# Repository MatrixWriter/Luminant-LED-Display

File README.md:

Luminant LED Display
====================

A large format, ultra bright LED display using printed circuit board technology that uses the Teensy 3.1 microcontroller and OctoWS2811 libraries.  The technology and design behind this project will result in a product that can be used for a broad range of commercial and hobbyist applications. 

LED Type: WS2812B

Designed and engineered by JP Allport <br>

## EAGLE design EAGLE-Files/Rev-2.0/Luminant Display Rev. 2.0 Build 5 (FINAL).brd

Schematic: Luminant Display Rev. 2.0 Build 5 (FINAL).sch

Parts (part):
C1, C2, C3, C4, C5, C6, C7, C8, C9, C10, C11, C12, C13, C14, C15, C16, C17, C18, C19, C20, C21, C22, C23, C24, C25, C26, C27, C28, C29, C30, C31, C32, C33, C34, C35, C36, C37, C38, C39, C40, C41, C42, C43, C44, C45, C46, C47, C48, C49, C50, C51, C52, C53, C54, C55, C56, C57, C58, C59, C60, C101, C102, C103, C104, C105, C106, C107, C108, C109, C110, C111, C112, C113, C114, C115, C116, C117, C118, C119, C120, C121, C122, C123, C124, C125, C126, C127, C128, C129, C130, C131, C132, C133, C134, C135, C136, C137, C138, C139, C140, C141, C142, C143, C144, C145, C146, C147, C148, C149, C150, C151, C152, C153, C154, C155, C156, C157, C158, C159, C160, C161, C162, C163, C164, C165, C166, C167, C168, C169, C170, C171, C172, C173, C174, C175, C176, C177, C178, C179, C180, C181, C182, C183, C184, C185, C186, C187, C188, C189, C190, C191, C192, C193, C194, C195, C196, C197, C198, C199, C200, C201, C202, C203, C204, C205, C206, C207, C208, C209, C210, C211, C212, C213, C214, C215, C216, C217, C218, C219, C220, C261, C262, C263, C264, C265, C266, C267, C268, C269, C270, C271, C272, C273, C274, C275, C276, C277, C278, C279, C280, C281, C282, C283, C284, C285, C286, C287, C288, C289, C290, C291, C292, C293, C294, C295, C296, C297, C298, C299, C300, C301, C302, C303, C304, C305, C306, C307, C308, C309, C310, C311, C312, C313, C314, C315, C316, C317, C318, C319, C320, C321, C322, C323, C324, C325, C326, C327, C328, C329, C330, C331, C332, C333, C334, C335, C336, C337, C338, C339, C340, C341, C342, C343, C344, C345, C346, C347, C348, C349, C350, C351, C352, C353, C354, C355, C356, C357, C358, C359, C360, C361, C362, C363, C364, C365, C366, C367, C368, C369, C370, C371, C372, C373, C374, C375, C376, C377, C378, C379, C380, C421, C422, C423, C424, C425, C426, C427, C428, C429, C430, C431, C432, C433, C434, C435, C436, C437, C438, C439, C440, C441, C442, C443, C444, C445, C446, C447, C448, C449, C450, C451, C452, C453, C454, C455, C456, C457, C458, C459, C460, C461, C462, C463, C464, C465, C466, C467, C468, C469, C470, C471, C472, C473, C474, C475, C476, C477, C478, C479, C480, C481, C482, C483, C484, C485, C486, C487, C488, C489, C490, C491, C492, C493, C494, C495, C496, C497, C498, C499, C500, C501, C502, C503, C504, C505, C506, C507, C508, C509, C510, C511, C512, C513, C514, C515, C516, C517, C518, C519, C520, C521, C522, C523, C524, C525, C526, C527, C528, C529, C530, C531, C532, C533, C534, C535, C536, C537, C538, C539, C540, C581, C582, C583, C584, C585, C586, C587, C588, C589, C590, C591, C592, C593, C594, C595, C596, C597, C598, C599, C600, C601, C602, C603, C604, C605, C606, C607, C608, C609, C610, C611, C612, C613, C614, C615, C616, C617, C618, C619, C620, C621, C622, C623, C624, C625, C626, C627, C628, C629, C630, C631, C632, C633, C634, C635, C636, C637, C638, C639, C640, C641, C642, C643, C644, C645, C646, C647, C648, C649, C650, C651, C652, C653, C654, C655, C656, C657, C658, C659, C660, C661, C662, C663, C664, C665, C666, C667, C668, C669, C670, C671, C672, C673, C674, C675, C676, C677, C678, C679, C680, C681, C682, C683, C684, C685, C686, C687, C688, C689, C690, C691, C692, C693, C694, C695, C696, C697, C698, C699, C700, C741, C742, C743, C744, C745, C746, C747, C748, C749, C750, C751, C752, C753, C754, C755, C756, C757, C758, C759, C760, C761, C762, C763, C764, C765, C766, C767, C768, C769, C770, C771, C772, C773, C774, C775, C776, C777, C778, C779, C780, C781, C782, C783, C784, C785, C786, C787, C788, C789, C790, C791, C792, C793, C794, C795, C796, C797, C798, C799, C800, C801, C802, C803, C804, C805, C806, C807, C808, C809, C810, C811, C812, C813, C814, C815, C816, C817, C818, C819, C820, C821, C822, C823, C824, C825, C826, C827, C828, C829, C830, C831, C832, C833, C834, C835, C836, C837, C838, C839, C840, C841, C842, C843, C844, C845, C846, C847, C848, C849, C850, C851, C852, C853, C854, C855, C856, C857, C858, C859, C860, C901, C902, C903, C904, C905, C906, C907, C908, C909, C910, C911, C912, C913, C914, C915, C916, C917, C918, C919, C920, C921, C922, C923, C924, C925, C926, C927, C928, C929, C930, C931, C932, C933, C934, C935, C936, C937, C938, C939, C940, C941, C942, C943, C944, C945, C946, C947, C948, C949, C950, C951, C952, C953, C954, C955, C956, C957, C958, C959, C960, C961, C962, C963, C964, C965, C966, C967, C968, C969, C970, C971, C972, C973, C974, C975, C976, C977, C978, C979, C980, C981, C982, C983, C984, C985, C986, C987, C988, C989, C990, C991, C992, C993, C994, C995, C996, C997, C998, C999, C1000, C1001, C1002, C1003, C1004, C1005, C1006, C1007, C1008, C1009, C1010, C1011, C1012, C1013, C1014, C1015, C1016, C1017, C1018, C1019, C1020, C1061, C1062, C1063, C1064, C1065, C1066, C1067, C1068, C1069, C1070, C1071, C1072, C1073, C1074, C1075, C1076, C1077, C1078, C1079, C1080, C1081, C1082, C1083, C1084, C1085, C1086, C1087, C1088, C1089, C1090, C1091, C1092, C1093, C1094, C1095, C1096, C1097, C1098, C1099, C1100, C1101, C1102, C1103, C1104, C1105, C1106, C1107, C1108, C1109, C1110, C1111, C1112, C1113, C1114, C1115, C1116, C1117, C1118, C1119, C1120, C1121, C1122, C1123, C1124, C1125, C1126, C1127, C1128, C1129, C1130, C1131, C1132, C1133, C1134, C1135, C1136, C1137, C1138, C1139, C1140, C1141, C1142, C1143, C1144, C1145, C1146, C1147, C1148, C1149, C1150, C1151, C1152, C1153, C1154, C1155, C1156, C1157, C1158, C1159, C1160, C1161, C1162, C1163, C1164, C1165, C1166, C1167, C1168, C1169, C1170, C1171, C1172, C1173, C1174, C1175, C1176, C1177, C1178, C1179, C1180, C1221, C1222, C1223, C1224, C1225, C1226, C1227, C1228, C1229, C1230, C1231, C1232, C1233, C1234, C1235, C1236, C1237, C1238, C1239, C1240, C1241, C1242, C1243, C1244, C1245, C1246, C1247, C1248, C1249, C1250, C1251, C1252, C1253, C1254, C1255, C1256, C1257, C1258, C1259, C1260, C1261, C1262, C1263, C1264, C1265, C1266, C1267, C1268, C1269, C1270, C1271, C1272, C1273, C1274, C1275, C1276, C1277, C1278, C1279, C1280, C1281, C1282, C1283, C1284, C1285, C1286, C1287, C1288, C1289, C1290, C1291, C1292, C1293, C1294, C1295, C1296, C1297, C1298, C1299, C1300, C1301, C1302, C1303, C1304, C1305, C1306, C1307, C1308, C1309, C1310, C1311, C1312, C1313, C1314, C1315, C1316, C1317, C1318, C1319, C1320, C1321, C1322, C1323, C1324, C1325, C1326, C1327, C1328, C1329, C1330, C1331, C1332, C1333, C1334, C1335, C1336, C1337, C1338, C1339, C1340, C1381, C1382, C1383, C1384, C1385, C1386, C1387, C1388, C1389, C1390, C1391, C1392, C1393, C1394, C1395, C1396, C1397, C1398, C1399, C1400, C1401, C1402, C1403, C1404, C1405, C1406, C1407, C1408, C1409, C1410, C1411, C1412, C1413, C1414, C1415, C1416, C1417, C1418, C1419, C1420, C1421, C1422, C1423, C1424, C1425, C1426, C1427, C1428, C1429, C1430, C1431, C1432, C1433, C1434, C1435, C1436, C1437, C1438, C1439, C1440, C1441, C1442, C1443, C1444, C1445, C1446, C1447, C1448, C1449, C1450, C1451, C1452, C1453, C1454, C1455, C1456, C1457, C1458, C1459, C1460, C1461, C1462, C1463, C1464, C1465, C1466, C1467, C1468, C1469, C1470, C1471, C1472, C1473, C1474, C1475, C1476, C1477, C1478, C1479, C1480, C1481, C1482, C1483, C1484, C1485, C1486, C1487, C1488, C1489, C1490, C1491, C1492, C1493, C1494, C1495, C1496, C1497, C1498, C1499, C1500, C1541, C1542, C1543, C1544, C1545, C1546, C1547, C1548, C1549, C1550, C1551, C1552, C1553, C1554, C1555, C1556, C1557, C1558, C1559, C1560, C1561, C1562, C1563, C1564, C1565, C1566, C1567, C1568, C1569, C1570, C1571, C1572, C1573, C1574, C1575, C1576, C1577, C1578, C1579, C1580, C1581, C1582, C1583, C1584, C1585, C1586, C1587, C1588, C1589, C1590, C1591, C1592, C1593, C1594, C1595, C1596, C1597, C1598, C1599, C1600, C1601, C1602, C1603, C1604, C1605, C1606, C1607, C1608, C1609, C1610, C1611, C1612, C1613, C1614, C1615, C1616, C1617, C1618, C1619, C1620, C1621, C1622, C1623, C1624, C1625, C1626, C1627, C1628, C1629, C1630, C1631, C1632, C1633, C1634, C1635, C1636, C1637, C1638, C1639, C1640, C1641, C1642, C1643, C1644, C1645, C1646, C1647, C1648, C1649, C1650, C1651, C1652, C1653, C1654, C1655, C1656, C1657, C1658, C1659, C1660, C1701, C1702, C1703, C1704, C1705, C1706, C1707, C1708, C1709, C1710, C1711, C1712, C1713, C1714, C1715, C1716, C1717, C1718, C1719, C1720, C1721, C1722, C1723, C1724, C1725, C1726, C1727, C1728, C1729, C1730, C1731, C1732, C1733, C1734, C1735, C1736, C1737, C1738, C1739, C1740, C1741, C1742, C1743, C1744, C1745, C1746, C1747, C1748, C1749, C1750, C1751, C1752, C1753, C1754, C1755, C1756, C1757, C1758, C1759, C1760, C1761, C1762, C1763, C1764, C1765, C1766, C1767, C1768, C1769, C1770, C1771, C1772, C1773, C1774, C1775, C1776, C1777, C1778, C1779, C1780, C1781, C1782, C1783, C1784, C1785, C1786, C1787, C1788, C1789, C1790, C1791, C1792, C1793, C1794, C1795, C1796, C1797, C1798, C1799, C1800, C1801, C1802, C1803, C1804, C1805, C1806, C1807, C1808, C1809, C1810, C1811, C1812, C1813, C1814, C1815, C1816, C1817, C1818, C1819, C1820, C1861, C1862, C1863, C1864, C1865, C1866, C1867, C1868, C1869, C1870, C1871, C1872, C1873, C1874, C1875, C1876, C1877, C1878, C1879, C1880, C1881, C1882, C1883, C1884, C1885, C1886, C1887, C1888, C1889, C1890, C1891, C1892, C1893, C1894, C1895, C1896, C1897, C1898, C1899, C1900, C1901, C1902, C1903, C1904, C1905, C1906, C1907, C1908, C1909, C1910, C1911, C1912, C1913, C1914, C1915, C1916, C1917, C1918, C1919, C1920, C1921, C1922, C1923, C1924, C1925, C1926, C1927, C1928, C1929, C1930, C1931, C1932, C1933, C1934, C1935, C1936, C1937, C1938, C1939, C1940, C1941, C1942, C1943, C1944, C1945, C1946, C1947, C1948, C1949, C1950, C1951, C1952, C1953, C1954, C1955, C1956, C1957, C1958, C1959, C1960, C1961, C1962, C1963, C1964, C1965, C1966, C1967, C1968, C1969, C1970, C1971, C1972, C1973, C1974, C1975, C1976, C1977, C1978, C1979, C1980, C2021, C2022, C2023, C2024, C2025, C2026, C2027, C2028, C2029, C2030, C2031, C2032, C2033, C2034, C2035, C2036, C2037, C2038, C2039, C2040, C2041, C2042, C2043, C2044, C2045, C2046, C2047, C2048, C2049, C2050, C2051, C2052, C2053, C2054, C2055, C2056, C2057, C2058, C2059, C2060, C2061, C2062, C2063, C2064, C2065, C2066, C2067, C2068, C2069, C2070, C2071, C2072, C2073, C2074, C2075, C2076, C2077, C2078, C2079, C2080, C2081, C2082, C2083, C2084, C2085, C2086, C2087, C2088, C2089, C2090, C2091, C2092, C2093, C2094, C2095, C2096, C2097, C2098, C2099, C2100, C2101, C2102, C2103, C2104, C2105, C2106, C2107, C2108, C2109, C2110, C2111, C2112, C2113, C2114, C2115, C2116, C2117, C2118, C2119, C2120, C2121, C2122, C2123, C2124, C2125, C2126, C2127, C2128, C2129, C2130, C2131, C2132, C2133, C2134, C2135, C2136, C2137, C2138, C2139, C2140, C2181, C2182, C2183, C2184, C2185, C2186, C2187, C2188, C2189, C2190, C2191, C2192, C2193, C2194, C2195, C2196, C2197, C2198, C2199, C2200, C2201, C2202, C2203, C2204, C2205, C2206, C2207, C2208, C2209, C2210, C2211, C2212, C2213, C2214, C2215, C2216, C2217, C2218, C2219, C2220, C2221, C2222, C2223, C2224, C2225, C2226, C2227, C2228, C2229, C2230, C2231, C2232, C2233, C2234, C2235, C2236, C2237, C2238, C2239, C2240, C2241, C2242, C2243, C2244, C2245, C2246, C2247, C2248, C2249, C2250, C2251, C2252, C2253, C2254, C2255, C2256, C2257, C2258, C2259, C2260, C2261, C2262, C2263, C2264, C2265, C2266, C2267, C2268, C2269, C2270, C2271, C2272, C2273, C2274, C2275, C2276, C2277, C2278, C2279, C2280, C2281, C2282, C2283, C2284, C2285, C2286, C2287, C2288, C2289, C2290, C2291, C2292, C2293, C2294, C2295, C2296, C2297, C2298, C2299, C2300, C2341, C2342, C2343, C2344, C2345, C2346, C2347, C2348, C2349, C2350, C2351, C2352, C2353, C2354, C2355, C2356, C2357, C2358, C2359, C2360, C2361, C2362, C2363, C2364, C2365, C2366, C2367, C2368, C2369, C2370, C2371, C2372, C2373, C2374, C2375, C2376, C2377, C2378, C2379, C2380, C2381, C2382, C2383, C2384, C2385, C2386, C2387, C2388, C2389, C2390, C2391, C2392, C2393, C2394, C2395, C2396, C2397, C2398, C2399, C2400, C2401, C2402, C2403, C2404, C2405, C2406, C2407, C2408, C2409, C2410, C2411, C2412, C2413, C2414, C2415, C2416, C2417, C2418, C2419, C2420, C2421, C2422, C2423, C2424, C2425, C2426, C2427, C2428, C2429, C2430, C2431, C2432, C2433, C2434, C2435, C2436, C2437, C2438, C2439, C2440, C2441, C2442, C2443, C2444, C2445, C2446, C2447, C2448, C2449, C2450, C2451, C2452, C2453, C2454, C2455, C2456, C2457, C2458, C2459, C2460, C2501, C2502, C2503, C2504, C2505, C2506, C2507, C2508, C2509, C2510, C2511, C2512, C2513, C2514, C2515, C2516, C2517, C2518, C2519, C2520, C2521, C2522, C2523, C2524, C2525, C2526, C2527, C2528, C2529, C2530, C2531, C2532, C2533, C2534, C2535, C2536, C2537, C2538, C2539, C2540, C2541, C2542, C2543, C2544, C2545, C2546, C2547, C2548, C2549, C2550, C2551, C2552, C2553, C2554, C2555, C2556, C2557, C2558, C2559, C2560: 0.1uF; 0805
C61, C64: CPOL-EU-PANASONIC_FK_V_H; PANASONIC_FK_V_H
C62, C63: CAP_POLE; PANASONIC_E
C65: CAP_POLC; PANASONIC_C
CAP-IC1-OPTIONAL, CAP-IC2-OPTIONAL: 0.1uF; 1206
IC1, IC2: 74HCT245N; DIL20
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
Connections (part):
3.3V: TEENSY1.3.3V, TEENSY1.3.3V1 (3.3V), TEENSY2.3.3V, TEENSY2.3.3V1 (3.3V)
5V-POWER: C1.1, C2.1, C3.1, C4.1, C5.1, C6.1, C7.1, C8.1, C9.1, C10.1, C11.1, C12.1, C13.1, C14.1, C15.1, C16.1, C17.1, C18.1, C19.1, C20.1, C21.1, C22.1, C23.1, C24.1, C25.1, C26.1, C27.1, C28.1, C29.1, C30.1, C31.1, C32.1, C33.1, C34.1, C35.1, C36.1, C37.1, C38.1, C39.1, C40.1, C41.1, C42.1, C43.1, C44.1, C45.1, C46.1, C47.1, C48.1, C49.1, C50.1, C51.1, C52.1, C53.1, C54.1, C55.1, C56.1, C57.1, C58.1, C59.1, C60.1, C61.+, C62.+, C63.+, C64.+, C101.1, C102.1, C103.1, C104.1, C105.1, C106.1, C107.1, C108.1, C109.1, C110.1, C111.1, C112.1, C113.1, C114.1, C115.1, C116.1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
AGND: TEENSY1.AGND, TEENSY2.AGND
DIN-1-IC1: LED60.4 (DI), R16.2
DIN-1-IC2: LED1340.4 (DI), R32.2
DIN-2-IC1: LED220.4 (DI), R15.2
DIN-2-IC2: LED1500.4 (DI), R31.2
DIN-3-IC1: LED380.4 (DI), R14.2
DIN-3-IC2: LED1660.4 (DI), R30.2
DIN-4-IC1: LED540.4 (DI), R13.2
DIN-4-IC2: LED1820.4 (DI), R29.2
DIN-5-IC1: LED700.4 (DI), R12.2
DIN-5-IC2: LED1980.4 (DI), R28.2
DIN-6-IC1: LED860.4 (DI), R11.2
DIN-6-IC2: LED2140.4 (DI), R27.2
DIN-7-IC1: LED1020.4 (DI), R10.2
DIN-7-IC2: LED2300.4 (DI), R26.2
DIN-8-IC1: LED1180.4 (DI), R9.2
DIN-8-IC2: LED2460.4 (DI), R25.2
FRAME-SYNC: TEENSY1.12 (12/MISO), TEENSY2.12 (12/MISO)
GND: C1.2, C2.2, C3.2, C4.2, C5.2, C6.2, C7.2, C8.2, C9.2, C10.2, C11.2, C12.2, C13.2, C14.2, C15.2, C16.2, C17.2, C18.2, C19.2, C20.2, C21.2, C22.2, C23.2, C24.2, C25.2, C26.2, C27.2, C28.2, C29.2, C30.2, C31.2, C32.2, C33.2, C34.2, C35.2, C36.2, C37.2, C38.2, C39.2, C40.2, C41.2, C42.2, C43.2, C44.2, C45.2, C46.2, C47.2, C48.2, C49.2, C50.2, C51.2, C52.2, C53.2, C54.2, C55.2, C56.2, C57.2, C58.2, C59.2, C60.2, C61.-, C62.-, C63.-, C64.-, C65.-, C101.2, C102.2, C103.2, C104.2, C105.2, C106.2, C107.2, C108.2, C109.2, C110.2, C111.2, C112.2, C113.2, C114.2, C115.2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
unnamed: LED1.4 (DI), LED2.2 (DO)
unnamed: LED3.4 (DI), LED4.2 (DO)
unnamed: LED2.4 (DI), LED3.2 (DO)
unnamed: LED5.4 (DI), LED6.2 (DO)
unnamed: LED7.4 (DI), LED8.2 (DO)
unnamed: LED6.4 (DI), LED7.2 (DO)
unnamed: LED4.4 (DI), LED5.2 (DO)
unnamed: LED9.4 (DI), LED10.2 (DO)
unnamed: LED11.4 (DI), LED12.2 (DO)
unnamed: LED10.4 (DI), LED11.2 (DO)
unnamed: LED13.4 (DI), LED14.2 (DO)
unnamed: LED15.4 (DI), LED16.2 (DO)
unnamed: LED14.4 (DI), LED15.2 (DO)
unnamed: LED12.4 (DI), LED13.2 (DO)
unnamed: LED8.4 (DI), LED9.2 (DO)
unnamed: LED17.4 (DI), LED18.2 (DO)
unnamed: LED19.4 (DI), LED20.2 (DO)
unnamed: LED18.4 (DI), LED19.2 (DO)
unnamed: LED21.4 (DI), LED22.2 (DO)
unnamed: LED23.4 (DI), LED24.2 (DO)
unnamed: LED22.4 (DI), LED23.2 (DO)
unnamed: LED20.4 (DI), LED21.2 (DO)
unnamed: LED25.4 (DI), LED26.2 (DO)
unnamed: LED27.4 (DI), LED28.2 (DO)
unnamed: LED26.4 (DI), LED27.2 (DO)
unnamed: LED29.4 (DI), LED30.2 (DO)
unnamed: LED31.4 (DI), LED32.2 (DO)
unnamed: LED30.4 (DI), LED31.2 (DO)
unnamed: LED28.4 (DI), LED29.2 (DO)
unnamed: LED24.4 (DI), LED25.2 (DO)
unnamed: LED16.4 (DI), LED17.2 (DO)
unnamed: LED33.4 (DI), LED34.2 (DO)
unnamed: LED35.4 (DI), LED36.2 (DO)
unnamed: LED34.4 (DI), LED35.2 (DO)
unnamed: LED37.4 (DI), LED38.2 (DO)
unnamed: LED39.4 (DI), LED40.2 (DO)
unnamed: LED38.4 (DI), LED39.2 (DO)
unnamed: LED36.4 (DI), LED37.2 (DO)
unnamed: LED41.4 (DI), LED42.2 (DO)
unnamed: LED43.4 (DI), LED44.2 (DO)
unnamed: LED42.4 (DI), LED43.2 (DO)
unnamed: LED45.4 (DI), LED46.2 (DO)
unnamed: LED47.4 (DI), LED48.2 (DO)
unnamed: LED46.4 (DI), LED47.2 (DO)
unnamed: LED44.4 (DI), LED45.2 (DO)
unnamed: LED40.4 (DI), LED41.2 (DO)
unnamed: LED49.4 (DI), LED50.2 (DO)
unnamed: LED51.4 (DI), LED52.2 (DO)
unnamed: LED50.4 (DI), LED51.2 (DO)
unnamed: LED53.4 (DI), LED54.2 (DO)
unnamed: LED55.4 (DI), LED56.2 (DO)
unnamed: LED54.4 (DI), LED55.2 (DO)
unnamed: LED52.4 (DI), LED53.2 (DO)
unnamed: LED57.4 (DI), LED58.2 (DO)
unnamed: LED59.4 (DI), LED60.2 (DO)
unnamed: LED58.4 (DI), LED59.2 (DO)
unnamed: LED56.4 (DI), LED57.2 (DO)
unnamed: LED48.4 (DI), LED49.2 (DO)
unnamed: LED32.4 (DI), LED33.2 (DO)
unnamed: IC2.1 (DIR), VCC-PAD11.TP
unnamed: LED101.4 (DI), LED102.2 (DO)
unnamed: LED103.4 (DI), LED104.2 (DO)
unnamed: LED102.4 (DI), LED103.2 (DO)
unnamed: LED105.4 (DI), LED106.2 (DO)
unnamed: LED107.4 (DI), LED108.2 (DO)
unnamed: LED106.4 (DI), LED107.2 (DO)
unnamed: LED109.4 (DI), LED110.2 (DO)
unnamed: LED111.4 (DI), LED112.2 (DO)
unnamed: LED110.4 (DI), LED111.2 (DO)
unnamed: LED108.4 (DI), LED109.2 (DO)
unnamed: LED104.4 (DI), LED105.2 (DO)
unnamed: LED113.4 (DI), LED114.2 (DO)
unnamed: LED115.4 (DI), LED116.2 (DO)
unnamed: LED114.4 (DI), LED115.2 (DO)
unnamed: LED117.4 (DI), LED118.2 (DO)
unnamed: LED119.4 (DI), LED120.2 (DO)
unnamed: LED118.4 (DI), LED119.2 (DO)
unnamed: LED116.4 (DI), LED117.2 (DO)
unnamed: LED121.4 (DI), LED122.2 (DO)
unnamed: LED123.4 (DI), LED124.2 (DO)
unnamed: LED122.4 (DI), LED123.2 (DO)
unnamed: LED125.4 (DI), LED126.2 (DO)
unnamed: LED127.4 (DI), LED128.2 (DO)
unnamed: LED126.4 (DI), LED127.2 (DO)
unnamed: LED124.4 (DI), LED125.2 (DO)
unnamed: LED120.4 (DI), LED121.2 (DO)
unnamed: LED129.4 (DI), LED130.2 (DO)
unnamed: LED131.4 (DI), LED132.2 (DO)
unnamed: LED130.4 (DI), LED131.2 (DO)
unnamed: LED133.4 (DI), LED134.2 (DO)
unnamed: LED135.4 (DI), LED136.2 (DO)
unnamed: LED134.4 (DI), LED135.2 (DO)
unnamed: LED132.4 (DI), LED133.2 (DO)
unnamed: LED137.4 (DI), LED138.2 (DO)
unnamed: LED139.4 (DI), LED140.2 (DO)
unnamed: LED138.4 (DI), LED139.2 (DO)
unnamed: LED141.4 (DI), LED142.2 (DO)
unnamed: LED143.4 (DI), LED144.2 (DO)
unnamed: LED142.4 (DI), LED143.2 (DO)
unnamed: LED140.4 (DI), LED141.2 (DO)
unnamed: LED136.4 (DI), LED137.2 (DO)
unnamed: LED128.4 (DI), LED129.2 (DO)
unnamed: LED112.4 (DI), LED113.2 (DO)
unnamed: LED144.4 (DI), LED145.2 (DO)
unnamed: LED146.4 (DI), LED147.2 (DO)
unnamed: LED148.4 (DI), LED149.2 (DO)
unnamed: LED147.4 (DI), LED148.2 (DO)
unnamed: LED150.4 (DI), LED151.2 (DO)
unnamed: LED152.4 (DI), LED153.2 (DO)
unnamed: LED151.4 (DI), LED152.2 (DO)
unnamed: LED149.4 (DI), LED150.2 (DO)
unnamed: LED154.4 (DI), LED155.2 (DO)
unnamed: LED156.4 (DI), LED157.2 (DO)
unnamed: LED155.4 (DI), LED156.2 (DO)
unnamed: LED158.4 (DI), LED159.2 (DO)
unnamed: LED159.4 (DI), LED160.2 (DO)
unnamed: LED157.4 (DI), LED158.2 (DO)
unnamed: LED153.4 (DI), LED154.2 (DO)
unnamed: LED145.4 (DI), LED146.2 (DO)
unnamed: LED161.4 (DI), LED162.2 (DO)
unnamed: LED163.4 (DI), LED164.2 (DO)
unnamed: LED162.4 (DI), LED163.2 (DO)
unnamed: LED165.4 (DI), LED166.2 (DO)
unnamed: LED167.4 (DI), LED168.2 (DO)
unnamed: LED166.4 (DI), LED167.2 (DO)
unnamed: LED164.4 (DI), LED165.2 (DO)
unnamed: LED169.4 (DI), LED170.2 (DO)
unnamed: LED171.4 (DI), LED172.2 (DO)
unnamed: LED170.4 (DI), LED171.2 (DO)
unnamed: LED173.4 (DI), LED174.2 (DO)
unnamed: LED175.4 (DI), LED176.2 (DO)
unnamed: LED174.4 (DI), LED175.2 (DO)
unnamed: LED172.4 (DI), LED173.2 (DO)
unnamed: LED168.4 (DI), LED169.2 (DO)
unnamed: LED177.4 (DI), LED178.2 (DO)
unnamed: LED179.4 (DI), LED180.2 (DO)
unnamed: LED178.4 (DI), LED179.2 (DO)
unnamed: LED181.4 (DI), LED182.2 (DO)
unnamed: LED183.4 (DI), LED184.2 (DO)
unnamed: LED182.4 (DI), LED183.2 (DO)
unnamed: LED180.4 (DI), LED181.2 (DO)
unnamed: LED185.4 (DI), LED186.2 (DO)
unnamed: LED187.4 (DI), LED188.2 (DO)
unnamed: LED186.4 (DI), LED187.2 (DO)
unnamed: LED189.4 (DI), LED190.2 (DO)
unnamed: LED191.4 (DI), LED192.2 (DO)
unnamed: LED190.4 (DI), LED191.2 (DO)
unnamed: LED188.4 (DI), LED189.2 (DO)
unnamed: LED184.4 (DI), LED185.2 (DO)
unnamed: LED176.4 (DI), LED177.2 (DO)
unnamed: LED193.4 (DI), LED194.2 (DO)
unnamed: LED195.4 (DI), LED196.2 (DO)
unnamed: LED194.4 (DI), LED195.2 (DO)
unnamed: LED197.4 (DI), LED198.2 (DO)
unnamed: LED199.4 (DI), LED200.2 (DO)
unnamed: LED198.4 (DI), LED199.2 (DO)
unnamed: LED196.4 (DI), LED197.2 (DO)
unnamed: LED201.4 (DI), LED202.2 (DO)
unnamed: LED203.4 (DI), LED204.2 (DO)
unnamed: LED202.4 (DI), LED203.2 (DO)
unnamed: LED205.4 (DI), LED206.2 (DO)
unnamed: LED207.4 (DI), LED208.2 (DO)
unnamed: LED206.4 (DI), LED207.2 (DO)
unnamed: LED204.4 (DI), LED205.2 (DO)
unnamed: LED200.4 (DI), LED201.2 (DO)
unnamed: LED209.4 (DI), LED210.2 (DO)
unnamed: LED211.4 (DI), LED212.2 (DO)
unnamed: LED210.4 (DI), LED211.2 (DO)
unnamed: LED213.4 (DI), LED214.2 (DO)
unnamed: LED215.4 (DI), LED216.2 (DO)
unnamed: LED214.4 (DI), LED215.2 (DO)
unnamed: LED212.4 (DI), LED213.2 (DO)
unnamed: LED217.4 (DI), LED218.2 (DO)
unnamed: LED219.4 (DI), LED220.2 (DO)
unnamed: LED218.4 (DI), LED219.2 (DO)
unnamed: LED216.4 (DI), LED217.2 (DO)
unnamed: LED208.4 (DI), LED209.2 (DO)
unnamed: LED192.4 (DI), LED193.2 (DO)
unnamed: LED261.4 (DI), LED262.2 (DO)
unnamed: LED263.4 (DI), LED264.2 (DO)
unnamed: LED262.4 (DI), LED263.2 (DO)
unnamed: LED265.4 (DI), LED266.2 (DO)
unnamed: LED267.4 (DI), LED268.2 (DO)
unnamed: LED266.4 (DI), LED267.2 (DO)
unnamed: LED269.4 (DI), LED270.2 (DO)
unnamed: LED271.4 (DI), LED272.2 (DO)
unnamed: LED270.4 (DI), LED271.2 (DO)
unnamed: LED268.4 (DI), LED269.2 (DO)
unnamed: LED264.4 (DI), LED265.2 (DO)
unnamed: LED273.4 (DI), LED274.2 (DO)
unnamed: LED275.4 (DI), LED276.2 (DO)
unnamed: LED274.4 (DI), LED275.2 (DO)
unnamed: LED277.4 (DI), LED278.2 (DO)
unnamed: LED279.4 (DI), LED280.2 (DO)
unnamed: LED278.4 (DI), LED279.2 (DO)
unnamed: LED276.4 (DI), LED277.2 (DO)
unnamed: LED281.4 (DI), LED282.2 (DO)
unnamed: LED283.4 (DI), LED284.2 (DO)
unnamed: LED282.4 (DI), LED283.2 (DO)
unnamed: LED285.4 (DI), LED286.2 (DO)
unnamed: LED287.4 (DI), LED288.2 (DO)
unnamed: LED286.4 (DI), LED287.2 (DO)
unnamed: LED284.4 (DI), LED285.2 (DO)
unnamed: LED280.4 (DI), LED281.2 (DO)
unnamed: LED289.4 (DI), LED290.2 (DO)
unnamed: LED291.4 (DI), LED292.2 (DO)
unnamed: LED290.4 (DI), LED291.2 (DO)
unnamed: LED293.4 (DI), LED294.2 (DO)
unnamed: LED295.4 (DI), LED296.2 (DO)
unnamed: LED294.4 (DI), LED295.2 (DO)
unnamed: LED292.4 (DI), LED293.2 (DO)
unnamed: LED297.4 (DI), LED298.2 (DO)
unnamed: LED299.4 (DI), LED300.2 (DO)
unnamed: LED298.4 (DI), LED299.2 (DO)
unnamed: LED301.4 (DI), LED302.2 (DO)
unnamed: LED303.4 (DI), LED304.2 (DO)
unnamed: LED302.4 (DI), LED303.2 (DO)
unnamed: LED300.4 (DI), LED301.2 (DO)
unnamed: LED296.4 (DI), LED297.2 (DO)
unnamed: LED288.4 (DI), LED289.2 (DO)
unnamed: LED272.4 (DI), LED273.2 (DO)
unnamed: LED304.4 (DI), LED305.2 (DO)
unnamed: LED306.4 (DI), LED307.2 (DO)
unnamed: LED308.4 (DI), LED309.2 (DO)
unnamed: LED307.4 (DI), LED308.2 (DO)
unnamed: LED310.4 (DI), LED311.2 (DO)
unnamed: LED312.4 (DI), LED313.2 (DO)
unnamed: LED311.4 (DI), LED312.2 (DO)
unnamed: LED309.4 (DI), LED310.2 (DO)
unnamed: LED314.4 (DI), LED315.2 (DO)
unnamed: LED316.4 (DI), LED317.2 (DO)
unnamed: LED315.4 (DI), LED316.2 (DO)
unnamed: LED318.4 (DI), LED319.2 (DO)
unnamed: LED319.4 (DI), LED320.2 (DO)
unnamed: LED317.4 (DI), LED318.2 (DO)
unnamed: LED313.4 (DI), LED314.2 (DO)
unnamed: LED305.4 (DI), LED306.2 (DO)
unnamed: LED321.4 (DI), LED322.2 (DO)
unnamed: LED323.4 (DI), LED324.2 (DO)
unnamed: LED322.4 (DI), LED323.2 (DO)
unnamed: LED325.4 (DI), LED326.2 (DO)
unnamed: LED327.4 (DI), LED328.2 (DO)
unnamed: LED326.4 (DI), LED327.2 (DO)
unnamed: LED324.4 (DI), LED325.2 (DO)
unnamed: LED329.4 (DI), LED330.2 (DO)
unnamed: LED331.4 (DI), LED332.2 (DO)
unnamed: LED330.4 (DI), LED331.2 (DO)
unnamed: LED333.4 (DI), LED334.2 (DO)
unnamed: LED335.4 (DI), LED336.2 (DO)
unnamed: LED334.4 (DI), LED335.2 (DO)
unnamed: LED332.4 (DI), LED333.2 (DO)
unnamed: LED328.4 (DI), LED329.2 (DO)
unnamed: LED337.4 (DI), LED338.2 (DO)
unnamed: LED339.4 (DI), LED340.2 (DO)
unnamed: LED338.4 (DI), LED339.2 (DO)
unnamed: LED341.4 (DI), LED342.2 (DO)
unnamed: LED343.4 (DI), LED344.2 (DO)
unnamed: LED342.4 (DI), LED343.2 (DO)
unnamed: LED340.4 (DI), LED341.2 (DO)
unnamed: LED345.4 (DI), LED346.2 (DO)
unnamed: LED347.4 (DI), LED348.2 (DO)
unnamed: LED346.4 (DI), LED347.2 (DO)
unnamed: LED349.4 (DI), LED350.2 (DO)
unnamed: LED351.4 (DI), LED352.2 (DO)
unnamed: LED350.4 (DI), LED351.2 (DO)
unnamed: LED348.4 (DI), LED349.2 (DO)
unnamed: LED344.4 (DI), LED345.2 (DO)
unnamed: LED336.4 (DI), LED337.2 (DO)
unnamed: LED353.4 (DI), LED354.2 (DO)
unnamed: LED355.4 (DI), LED356.2 (DO)
unnamed: LED354.4 (DI), LED355.2 (DO)
unnamed: LED357.4 (DI), LED358.2 (DO)
unnamed: LED359.4 (DI), LED360.2 (DO)
unnamed: LED358.4 (DI), LED359.2 (DO)
unnamed: LED356.4 (DI), LED357.2 (DO)
unnamed: LED361.4 (DI), LED362.2 (DO)
unnamed: LED363.4 (DI), LED364.2 (DO)
unnamed: LED362.4 (DI), LED363.2 (DO)
unnamed: LED365.4 (DI), LED366.2 (DO)
unnamed: LED367.4 (DI), LED368.2 (DO)
unnamed: LED366.4 (DI), LED367.2 (DO)
unnamed: LED364.4 (DI), LED365.2 (DO)
unnamed: LED360.4 (DI), LED361.2 (DO)
unnamed: LED369.4 (DI), LED370.2 (DO)
unnamed: LED371.4 (DI), LED372.2 (DO)
unnamed: LED370.4 (DI), LED371.2 (DO)
unnamed: LED373.4 (DI), LED374.2 (DO)
unnamed: LED375.4 (DI), LED376.2 (DO)
unnamed: LED374.4 (DI), LED375.2 (DO)
unnamed: LED372.4 (DI), LED373.2 (DO)
unnamed: LED377.4 (DI), LED378.2 (DO)
unnamed: LED379.4 (DI), LED380.2 (DO)
unnamed: LED378.4 (DI), LED379.2 (DO)
unnamed: LED376.4 (DI), LED377.2 (DO)
unnamed: LED368.4 (DI), LED369.2 (DO)
unnamed: LED352.4 (DI), LED353.2 (DO)
unnamed: LED421.4 (DI), LED422.2 (DO)
unnamed: LED423.4 (DI), LED424.2 (DO)
unnamed: LED422.4 (DI), LED423.2 (DO)
unnamed: LED425.4 (DI), LED426.2 (DO)
unnamed: LED427.4 (DI), LED428.2 (DO)
unnamed: LED426.4 (DI), LED427.2 (DO)
unnamed: LED429.4 (DI), LED430.2 (DO)
unnamed: LED431.4 (DI), LED432.2 (DO)
unnamed: LED430.4 (DI), LED431.2 (DO)
unnamed: LED428.4 (DI), LED429.2 (DO)
unnamed: LED424.4 (DI), LED425.2 (DO)
unnamed: LED433.4 (DI), LED434.2 (DO)
unnamed: LED435.4 (DI), LED436.2 (DO)
unnamed: LED434.4 (DI), LED435.2 (DO)
unnamed: LED437.4 (DI), LED438.2 (DO)
unnamed: LED439.4 (DI), LED440.2 (DO)
unnamed: LED438.4 (DI), LED439.2 (DO)
unnamed: LED436.4 (DI), LED437.2 (DO)
unnamed: LED441.4 (DI), LED442.2 (DO)
unnamed: LED443.4 (DI), LED444.2 (DO)
unnamed: LED442.4 (DI), LED443.2 (DO)
unnamed: LED445.4 (DI), LED446.2 (DO)
unnamed: LED447.4 (DI), LED448.2 (DO)
unnamed: LED446.4 (DI), LED447.2 (DO)
unnamed: LED444.4 (DI), LED445.2 (DO)
unnamed: LED440.4 (DI), LED441.2 (DO)
unnamed: LED449.4 (DI), LED450.2 (DO)
unnamed: LED451.4 (DI), LED452.2 (DO)
unnamed: LED450.4 (DI), LED451.2 (DO)
unnamed: LED453.4 (DI), LED454.2 (DO)
unnamed: LED455.4 (DI), LED456.2 (DO)
unnamed: LED454.4 (DI), LED455.2 (DO)
unnamed: LED452.4 (DI), LED453.2 (DO)
unnamed: LED457.4 (DI), LED458.2 (DO)
unnamed: LED459.4 (DI), LED460.2 (DO)
unnamed: LED458.4 (DI), LED459.2 (DO)
unnamed: LED461.4 (DI), LED462.2 (DO)
unnamed: LED463.4 (DI), LED464.2 (DO)
unnamed: LED462.4 (DI), LED463.2 (DO)
unnamed: LED460.4 (DI), LED461.2 (DO)
unnamed: LED456.4 (DI), LED457.2 (DO)
unnamed: LED448.4 (DI), LED449.2 (DO)
unnamed: LED432.4 (DI), LED433.2 (DO)
unnamed: LED464.4 (DI), LED465.2 (DO)
unnamed: LED466.4 (DI), LED467.2 (DO)
unnamed: LED468.4 (DI), LED469.2 (DO)
unnamed: LED467.4 (DI), LED468.2 (DO)
unnamed: LED470.4 (DI), LED471.2 (DO)
unnamed: LED472.4 (DI), LED473.2 (DO)
unnamed: LED471.4 (DI), LED472.2 (DO)
unnamed: LED469.4 (DI), LED470.2 (DO)
unnamed: LED474.4 (DI), LED475.2 (DO)
unnamed: LED476.4 (DI), LED477.2 (DO)
unnamed: LED475.4 (DI), LED476.2 (DO)
unnamed: LED478.4 (DI), LED479.2 (DO)
unnamed: LED479.4 (DI), LED480.2 (DO)
unnamed: LED477.4 (DI), LED478.2 (DO)
unnamed: LED473.4 (DI), LED474.2 (DO)
unnamed: LED465.4 (DI), LED466.2 (DO)
unnamed: LED481.4 (DI), LED482.2 (DO)
unnamed: LED483.4 (DI), LED484.2 (DO)
unnamed: LED482.4 (DI), LED483.2 (DO)
unnamed: LED485.4 (DI), LED486.2 (DO)
unnamed: LED487.4 (DI), LED488.2 (DO)
unnamed: LED486.4 (DI), LED487.2 (DO)
unnamed: LED484.4 (DI), LED485.2 (DO)
unnamed: LED489.4 (DI), LED490.2 (DO)
unnamed: LED491.4 (DI), LED492.2 (DO)
unnamed: LED490.4 (DI), LED491.2 (DO)
unnamed: LED493.4 (DI), LED494.2 (DO)
unnamed: LED495.4 (DI), LED496.2 (DO)
unnamed: LED494.4 (DI), LED495.2 (DO)
unnamed: LED492.4 (DI), LED493.2 (DO)
unnamed: LED488.4 (DI), LED489.2 (DO)
unnamed: LED497.4 (DI), LED498.2 (DO)
unnamed: LED499.4 (DI), LED500.2 (DO)
unnamed: LED498.4 (DI), LED499.2 (DO)
unnamed: LED501.4 (DI), LED502.2 (DO)
unnamed: LED503.4 (DI), LED504.2 (DO)
unnamed: LED502.4 (DI), LED503.2 (DO)
unnamed: LED500.4 (DI), LED501.2 (DO)
unnamed: LED505.4 (DI), LED506.2 (DO)
unnamed: LED507.4 (DI), LED508.2 (DO)
unnamed: LED506.4 (DI), LED507.2 (DO)
unnamed: LED509.4 (DI), LED510.2 (DO)
unnamed: LED511.4 (DI), LED512.2 (DO)
unnamed: LED510.4 (DI), LED511.2 (DO)
unnamed: LED508.4 (DI), LED509.2 (DO)
unnamed: LED504.4 (DI), LED505.2 (DO)
unnamed: LED496.4 (DI), LED497.2 (DO)
unnamed: LED513.4 (DI), LED514.2 (DO)
unnamed: LED515.4 (DI), LED516.2 (DO)
unnamed: LED514.4 (DI), LED515.2 (DO)
unnamed: LED517.4 (DI), LED518.2 (DO)
unnamed: LED519.4 (DI), LED520.2 (DO)
unnamed: LED518.4 (DI), LED519.2 (DO)
unnamed: LED516.4 (DI), LED517.2 (DO)
unnamed: LED521.4 (DI), LED522.2 (DO)
unnamed: LED523.4 (DI), LED524.2 (DO)
unnamed: LED522.4 (DI), LED523.2 (DO)
unnamed: LED525.4 (DI), LED526.2 (DO)
unnamed: LED527.4 (DI), LED528.2 (DO)
unnamed: LED526.4 (DI), LED527.2 (DO)
unnamed: LED524.4 (DI), LED525.2 (DO)
unnamed: LED520.4 (DI), LED521.2 (DO)
unnamed: LED529.4 (DI), LED530.2 (DO)
unnamed: LED531.4 (DI), LED532.2 (DO)
unnamed: LED530.4 (DI), LED531.2 (DO)
unnamed: LED533.4 (DI), LED534.2 (DO)
unnamed: LED535.4 (DI), LED536.2 (DO)
unnamed: LED534.4 (DI), LED535.2 (DO)
unnamed: LED532.4 (DI), LED533.2 (DO)
unnamed: LED537.4 (DI), LED538.2 (DO)
unnamed: LED539.4 (DI), LED540.2 (DO)
unnamed: LED538.4 (DI), LED539.2 (DO)
unnamed: LED536.4 (DI), LED537.2 (DO)
unnamed: LED528.4 (DI), LED529.2 (DO)
unnamed: LED512.4 (DI), LED513.2 (DO)
unnamed: LED581.4 (DI), LED582.2 (DO)
unnamed: LED583.4 (DI), LED584.2 (DO)
unnamed: LED582.4 (DI), LED583.2 (DO)
unnamed: LED585.4 (DI), LED586.2 (DO)
unnamed: LED587.4 (DI), LED588.2 (DO)
unnamed: LED586.4 (DI), LED587.2 (DO)
unnamed: LED589.4 (DI), LED590.2 (DO)
unnamed: LED591.4 (DI), LED592.2 (DO)
unnamed: LED590.4 (DI), LED591.2 (DO)
unnamed: LED588.4 (DI), LED589.2 (DO)
unnamed: LED584.4 (DI), LED585.2 (DO)
unnamed: LED593.4 (DI), LED594.2 (DO)
unnamed: LED595.4 (DI), LED596.2 (DO)
unnamed: LED594.4 (DI), LED595.2 (DO)
unnamed: LED597.4 (DI), LED598.2 (DO)
unnamed: LED599.4 (DI), LED600.2 (DO)
unnamed: LED598.4 (DI), LED599.2 (DO)
unnamed: LED596.4 (DI), LED597.2 (DO)
unnamed: LED601.4 (DI), LED602.2 (DO)
unnamed: LED603.4 (DI), LED604.2 (DO)
unnamed: LED602.4 (DI), LED603.2 (DO)
unnamed: LED605.4 (DI), LED606.2 (DO)
unnamed: LED607.4 (DI), LED608.2 (DO)
unnamed: LED606.4 (DI), LED607.2 (DO)
unnamed: LED604.4 (DI), LED605.2 (DO)
unnamed: LED600.4 (DI), LED601.2 (DO)
unnamed: LED609.4 (DI), LED610.2 (DO)
unnamed: LED611.4 (DI), LED612.2 (DO)
unnamed: LED610.4 (DI), LED611.2 (DO)
unnamed: LED613.4 (DI), LED614.2 (DO)
unnamed: LED615.4 (DI), LED616.2 (DO)
unnamed: LED614.4 (DI), LED615.2 (DO)
unnamed: LED612.4 (DI), LED613.2 (DO)
unnamed: LED617.4 (DI), LED618.2 (DO)
unnamed: LED619.4 (DI), LED620.2 (DO)
unnamed: LED618.4 (DI), LED619.2 (DO)
unnamed: LED621.4 (DI), LED622.2 (DO)
unnamed: LED623.4 (DI), LED624.2 (DO)
unnamed: LED622.4 (DI), LED623.2 (DO)
unnamed: LED620.4 (DI), LED621.2 (DO)
unnamed: LED616.4 (DI), LED617.2 (DO)
unnamed: LED608.4 (DI), LED609.2 (DO)
unnamed: LED592.4 (DI), LED593.2 (DO)
unnamed: LED624.4 (DI), LED625.2 (DO)
unnamed: LED626.4 (DI), LED627.2 (DO)
unnamed: LED628.4 (DI), LED629.2 (DO)
unnamed: LED627.4 (DI), LED628.2 (DO)
unnamed: LED630.4 (DI), LED631.2 (DO)
unnamed: LED632.4 (DI), LED633.2 (DO)
unnamed: LED631.4 (DI), LED632.2 (DO)
unnamed: LED629.4 (DI), LED630.2 (DO)
unnamed: LED634.4 (DI), LED635.2 (DO)
unnamed: LED636.4 (DI), LED637.2 (DO)
unnamed: LED635.4 (DI), LED636.2 (DO)
unnamed: LED638.4 (DI), LED639.2 (DO)
unnamed: LED639.4 (DI), LED640.2 (DO)
unnamed: LED637.4 (DI), LED638.2 (DO)
unnamed: LED633.4 (DI), LED634.2 (DO)
unnamed: LED625.4 (DI), LED626.2 (DO)
unnamed: LED641.4 (DI), LED642.2 (DO)
unnamed: LED643.4 (DI), LED644.2 (DO)
unnamed: LED642.4 (DI), LED643.2 (DO)
unnamed: LED645.4 (DI), LED646.2 (DO)
unnamed: LED647.4 (DI), LED648.2 (DO)
unnamed: LED646.4 (DI), LED647.2 (DO)
unnamed: LED644.4 (DI), LED645.2 (DO)
unnamed: LED649.4 (DI), LED650.2 (DO)
unnamed: LED651.4 (DI), LED652.2 (DO)
unnamed: LED650.4 (DI), LED651.2 (DO)
unnamed: LED653.4 (DI), LED654.2 (DO)
unnamed: LED655.4 (DI), LED656.2 (DO)
unnamed: LED654.4 (DI), LED655.2 (DO)
unnamed: LED652.4 (DI), LED653.2 (DO)
unnamed: LED648.4 (DI), LED649.2 (DO)
unnamed: LED657.4 (DI), LED658.2 (DO)
unnamed: LED659.4 (DI), LED660.2 (DO)
unnamed: LED658.4 (DI), LED659.2 (DO)
unnamed: LED661.4 (DI), LED662.2 (DO)
unnamed: LED663.4 (DI), LED664.2 (DO)
unnamed: LED662.4 (DI), LED663.2 (DO)
unnamed: LED660.4 (DI), LED661.2 (DO)
unnamed: LED665.4 (DI), LED666.2 (DO)
unnamed: LED667.4 (DI), LED668.2 (DO)
unnamed: LED666.4 (DI), LED667.2 (DO)
unnamed: LED669.4 (DI), LED670.2 (DO)
unnamed: LED671.4 (DI), LED672.2 (DO)
unnamed: LED670.4 (DI), LED671.2 (DO)
unnamed: LED668.4 (DI), LED669.2 (DO)
unnamed: LED664.4 (DI), LED665.2 (DO)
unnamed: LED656.4 (DI), LED657.2 (DO)
unnamed: LED673.4 (DI), LED674.2 (DO)
unnamed: LED675.4 (DI), LED676.2 (DO)
unnamed: LED674.4 (DI), LED675.2 (DO)
unnamed: LED677.4 (DI), LED678.2 (DO)
unnamed: LED679.4 (DI), LED680.2 (DO)
unnamed: LED678.4 (DI), LED679.2 (DO)
unnamed: LED676.4 (DI), LED677.2 (DO)
unnamed: LED681.4 (DI), LED682.2 (DO)
unnamed: LED683.4 (DI), LED684.2 (DO)
unnamed: LED682.4 (DI), LED683.2 (DO)
unnamed: LED685.4 (DI), LED686.2 (DO)
unnamed: LED687.4 (DI), LED688.2 (DO)
unnamed: LED686.4 (DI), LED687.2 (DO)
unnamed: LED684.4 (DI), LED685.2 (DO)
unnamed: LED680.4 (DI), LED681.2 (DO)
unnamed: LED689.4 (DI), LED690.2 (DO)
unnamed: LED691.4 (DI), LED692.2 (DO)
unnamed: LED690.4 (DI), LED691.2 (DO)
unnamed: LED693.4 (DI), LED694.2 (DO)
unnamed: LED695.4 (DI), LED696.2 (DO)
unnamed: LED694.4 (DI), LED695.2 (DO)
unnamed: LED692.4 (DI), LED693.2 (DO)
unnamed: LED697.4 (DI), LED698.2 (DO)
unnamed: LED699.4 (DI), LED700.2 (DO)
unnamed: LED698.4 (DI), LED699.2 (DO)
unnamed: LED696.4 (DI), LED697.2 (DO)
unnamed: LED688.4 (DI), LED689.2 (DO)
unnamed: LED672.4 (DI), LED673.2 (DO)
unnamed: IC1.9 (A8), TEENSY1.2
unnamed: LED741.4 (DI), LED742.2 (DO)
unnamed: LED743.4 (DI), LED744.2 (DO)
unnamed: LED742.4 (DI), LED743.2 (DO)
unnamed: LED745.4 (DI), LED746.2 (DO)
unnamed: LED747.4 (DI), LED748.2 (DO)
unnamed: LED746.4 (DI), LED747.2 (DO)
unnamed: LED749.4 (DI), LED750.2 (DO)
unnamed: LED751.4 (DI), LED752.2 (DO)
unnamed: LED750.4 (DI), LED751.2 (DO)
unnamed: LED748.4 (DI), LED749.2 (DO)
unnamed: LED744.4 (DI), LED745.2 (DO)
unnamed: LED753.4 (DI), LED754.2 (DO)
unnamed: LED755.4 (DI), LED756.2 (DO)
unnamed: LED754.4 (DI), LED755.2 (DO)
unnamed: LED757.4 (DI), LED758.2 (DO)
unnamed: LED759.4 (DI), LED760.2 (DO)
unnamed: LED758.4 (DI), LED759.2 (DO)
unnamed: LED756.4 (DI), LED757.2 (DO)
unnamed: LED761.4 (DI), LED762.2 (DO)
unnamed: LED763.4 (DI), LED764.2 (DO)
unnamed: LED762.4 (DI), LED763.2 (DO)
unnamed: LED765.4 (DI), LED766.2 (DO)
unnamed: LED767.4 (DI), LED768.2 (DO)
unnamed: LED766.4 (DI), LED767.2 (DO)
unnamed: LED764.4 (DI), LED765.2 (DO)
unnamed: LED760.4 (DI), LED761.2 (DO)
unnamed: LED769.4 (DI), LED770.2 (DO)
unnamed: LED771.4 (DI), LED772.2 (DO)
unnamed: LED770.4 (DI), LED771.2 (DO)
unnamed: LED773.4 (DI), LED774.2 (DO)
unnamed: LED775.4 (DI), LED776.2 (DO)
unnamed: LED774.4 (DI), LED775.2 (DO)
unnamed: LED772.4 (DI), LED773.2 (DO)
unnamed: LED777.4 (DI), LED778.2 (DO)
unnamed: LED779.4 (DI), LED780.2 (DO)
unnamed: LED778.4 (DI), LED779.2 (DO)
unnamed: LED781.4 (DI), LED782.2 (DO)
unnamed: LED783.4 (DI), LED784.2 (DO)
unnamed: LED782.4 (DI), LED783.2 (DO)
unnamed: LED780.4 (DI), LED781.2 (DO)
unnamed: LED776.4 (DI), LED777.2 (DO)
unnamed: LED768.4 (DI), LED769.2 (DO)
unnamed: LED752.4 (DI), LED753.2 (DO)
unnamed: LED784.4 (DI), LED785.2 (DO)
unnamed: LED786.4 (DI), LED787.2 (DO)
unnamed: LED788.4 (DI), LED789.2 (DO)
unnamed: LED787.4 (DI), LED788.2 (DO)
unnamed: LED790.4 (DI), LED791.2 (DO)
unnamed: LED792.4 (DI), LED793.2 (DO)
unnamed: LED791.4 (DI), LED792.2 (DO)
unnamed: LED789.4 (DI), LED790.2 (DO)
unnamed: LED794.4 (DI), LED795.2 (DO)
unnamed: LED796.4 (DI), LED797.2 (DO)
unnamed: LED795.4 (DI), LED796.2 (DO)
unnamed: LED798.4 (DI), LED799.2 (DO)
unnamed: LED799.4 (DI), LED800.2 (DO)
unnamed: LED797.4 (DI), LED798.2 (DO)
unnamed: LED793.4 (DI), LED794.2 (DO)
unnamed: LED785.4 (DI), LED786.2 (DO)
unnamed: IC1.8 (A7), TEENSY1.14/A0
unnamed: LED801.4 (DI), LED802.2 (DO)
unnamed: LED803.4 (DI), LED804.2 (DO)
unnamed: LED802.4 (DI), LED803.2 (DO)
unnamed: LED805.4 (DI), LED806.2 (DO)
unnamed: LED807.4 (DI), LED808.2 (DO)
unnamed: LED806.4 (DI), LED807.2 (DO)
unnamed: LED804.4 (DI), LED805.2 (DO)
unnamed: LED809.4 (DI), LED810.2 (DO)
unnamed: LED811.4 (DI), LED812.2 (DO)
unnamed: LED810.4 (DI), LED811.2 (DO)
unnamed: LED813.4 (DI), LED814.2 (DO)
unnamed: LED815.4 (DI), LED816.2 (DO)
unnamed: LED814.4 (DI), LED815.2 (DO)
unnamed: LED812.4 (DI), LED813.2 (DO)
unnamed: LED808.4 (DI), LED809.2 (DO)
unnamed: LED817.4 (DI), LED818.2 (DO)
unnamed: LED819.4 (DI), LED820.2 (DO)
unnamed: LED818.4 (DI), LED819.2 (DO)
unnamed: LED821.4 (DI), LED822.2 (DO)
unnamed: LED823.4 (DI), LED824.2 (DO)
unnamed: LED822.4 (DI), LED823.2 (DO)
unnamed: LED820.4 (DI), LED821.2 (DO)
unnamed: LED825.4 (DI), LED826.2 (DO)
unnamed: LED827.4 (DI), LED828.2 (DO)
unnamed: LED826.4 (DI), LED827.2 (DO)
unnamed: LED829.4 (DI), LED830.2 (DO)
unnamed: LED831.4 (DI), LED832.2 (DO)
unnamed: LED830.4 (DI), LED831.2 (DO)
unnamed: LED828.4 (DI), LED829.2 (DO)
unnamed: LED824.4 (DI), LED825.2 (DO)
unnamed: LED816.4 (DI), LED817.2 (DO)
unnamed: LED833.4 (DI), LED834.2 (DO)
unnamed: LED835.4 (DI), LED836.2 (DO)
unnamed: LED834.4 (DI), LED835.2 (DO)
unnamed: LED837.4 (DI), LED838.2 (DO)
unnamed: LED839.4 (DI), LED840.2 (DO)
unnamed: LED838.4 (DI), LED839.2 (DO)
unnamed: LED836.4 (DI), LED837.2 (DO)
unnamed: LED841.4 (DI), LED842.2 (DO)
unnamed: LED843.4 (DI), LED844.2 (DO)
unnamed: LED842.4 (DI), LED843.2 (DO)
unnamed: LED845.4 (DI), LED846.2 (DO)
unnamed: LED847.4 (DI), LED848.2 (DO)
unnamed: LED846.4 (DI), LED847.2 (DO)
unnamed: LED844.4 (DI), LED845.2 (DO)
unnamed: LED840.4 (DI), LED841.2 (DO)
unnamed: LED849.4 (DI), LED850.2 (DO)
unnamed: LED851.4 (DI), LED852.2 (DO)
unnamed: LED850.4 (DI), LED851.2 (DO)
unnamed: LED853.4 (DI), LED854.2 (DO)
unnamed: LED855.4 (DI), LED856.2 (DO)
unnamed: LED854.4 (DI), LED855.2 (DO)
unnamed: LED852.4 (DI), LED853.2 (DO)
unnamed: LED857.4 (DI), LED858.2 (DO)
unnamed: LED859.4 (DI), LED860.2 (DO)
unnamed: LED858.4 (DI), LED859.2 (DO)
unnamed: LED856.4 (DI), LED857.2 (DO)
unnamed: LED848.4 (DI), LED849.2 (DO)
unnamed: LED832.4 (DI), LED833.2 (DO)
unnamed: IC1.7 (A6), TEENSY1.7 (7/RX3)
unnamed: LED901.4 (DI), LED902.2 (DO)
unnamed: LED903.4 (DI), LED904.2 (DO)
unnamed: LED902.4 (DI), LED903.2 (DO)
unnamed: LED905.4 (DI), LED906.2 (DO)
unnamed: LED907.4 (DI), LED908.2 (DO)
unnamed: LED906.4 (DI), LED907.2 (DO)
unnamed: LED909.4 (DI), LED910.2 (DO)
unnamed: LED911.4 (DI), LED912.2 (DO)
unnamed: LED910.4 (DI), LED911.2 (DO)
unnamed: LED908.4 (DI), LED909.2 (DO)
unnamed: LED904.4 (DI), LED905.2 (DO)
unnamed: LED913.4 (DI), LED914.2 (DO)
unnamed: LED915.4 (DI), LED916.2 (DO)
unnamed: LED914.4 (DI), LED915.2 (DO)
unnamed: LED917.4 (DI), LED918.2 (DO)
unnamed: LED919.4 (DI), LED920.2 (DO)
unnamed: LED918.4 (DI), LED919.2 (DO)
unnamed: LED916.4 (DI), LED917.2 (DO)
unnamed: LED921.4 (DI), LED922.2 (DO)
unnamed: LED923.4 (DI), LED924.2 (DO)
unnamed: LED922.4 (DI), LED923.2 (DO)
unnamed: LED925.4 (DI), LED926.2 (DO)
unnamed: LED927.4 (DI), LED928.2 (DO)
unnamed: LED926.4 (DI), LED927.2 (DO)
unnamed: LED924.4 (DI), LED925.2 (DO)
unnamed: LED920.4 (DI), LED921.2 (DO)
unnamed: LED929.4 (DI), LED930.2 (DO)
unnamed: LED931.4 (DI), LED932.2 (DO)
unnamed: LED930.4 (DI), LED931.2 (DO)
unnamed: LED933.4 (DI), LED934.2 (DO)
unnamed: LED935.4 (DI), LED936.2 (DO)
unnamed: LED934.4 (DI), LED935.2 (DO)
unnamed: LED932.4 (DI), LED933.2 (DO)
unnamed: LED937.4 (DI), LED938.2 (DO)
unnamed: LED939.4 (DI), LED940.2 (DO)
unnamed: LED938.4 (DI), LED939.2 (DO)
unnamed: LED941.4 (DI), LED942.2 (DO)
unnamed: LED943.4 (DI), LED944.2 (DO)
unnamed: LED942.4 (DI), LED943.2 (DO)
unnamed: LED940.4 (DI), LED941.2 (DO)
unnamed: LED936.4 (DI), LED937.2 (DO)
unnamed: LED928.4 (DI), LED929.2 (DO)
unnamed: LED912.4 (DI), LED913.2 (DO)
unnamed: LED944.4 (DI), LED945.2 (DO)
unnamed: LED946.4 (DI), LED947.2 (DO)
unnamed: LED948.4 (DI), LED949.2 (DO)
unnamed: LED947.4 (DI), LED948.2 (DO)
unnamed: LED950.4 (DI), LED951.2 (DO)
unnamed: LED952.4 (DI), LED953.2 (DO)
unnamed: LED951.4 (DI), LED952.2 (DO)
unnamed: LED949.4 (DI), LED950.2 (DO)
unnamed: LED954.4 (DI), LED955.2 (DO)
unnamed: LED956.4 (DI), LED957.2 (DO)
unnamed: LED955.4 (DI), LED956.2 (DO)
unnamed: LED958.4 (DI), LED959.2 (DO)
unnamed: LED959.4 (DI), LED960.2 (DO)
unnamed: LED957.4 (DI), LED958.2 (DO)
unnamed: LED953.4 (DI), LED954.2 (DO)
unnamed: LED945.4 (DI), LED946.2 (DO)
unnamed: IC1.6 (A5), TEENSY1.8 (8/TX3)
unnamed: LED961.4 (DI), LED962.2 (DO)
unnamed: LED963.4 (DI), LED964.2 (DO)
unnamed: LED962.4 (DI), LED963.2 (DO)
unnamed: LED965.4 (DI), LED966.2 (DO)
unnamed: LED967.4 (DI), LED968.2 (DO)
unnamed: LED966.4 (DI), LED967.2 (DO)
unnamed: LED964.4 (DI), LED965.2 (DO)
unnamed: LED969.4 (DI), LED970.2 (DO)
unnamed: LED971.4 (DI), LED972.2 (DO)
unnamed: LED970.4 (DI), LED971.2 (DO)
unnamed: LED973.4 (DI), LED974.2 (DO)
unnamed: LED975.4 (DI), LED976.2 (DO)
unnamed: LED974.4 (DI), LED975.2 (DO)
unnamed: LED972.4 (DI), LED973.2 (DO)
unnamed: LED968.4 (DI), LED969.2 (DO)
unnamed: LED977.4 (DI), LED978.2 (DO)
unnamed: LED979.4 (DI), LED980.2 (DO)
unnamed: LED978.4 (DI), LED979.2 (DO)
unnamed: LED981.4 (DI), LED982.2 (DO)
unnamed: LED983.4 (DI), LED984.2 (DO)
unnamed: LED982.4 (DI), LED983.2 (DO)
unnamed: LED980.4 (DI), LED981.2 (DO)
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
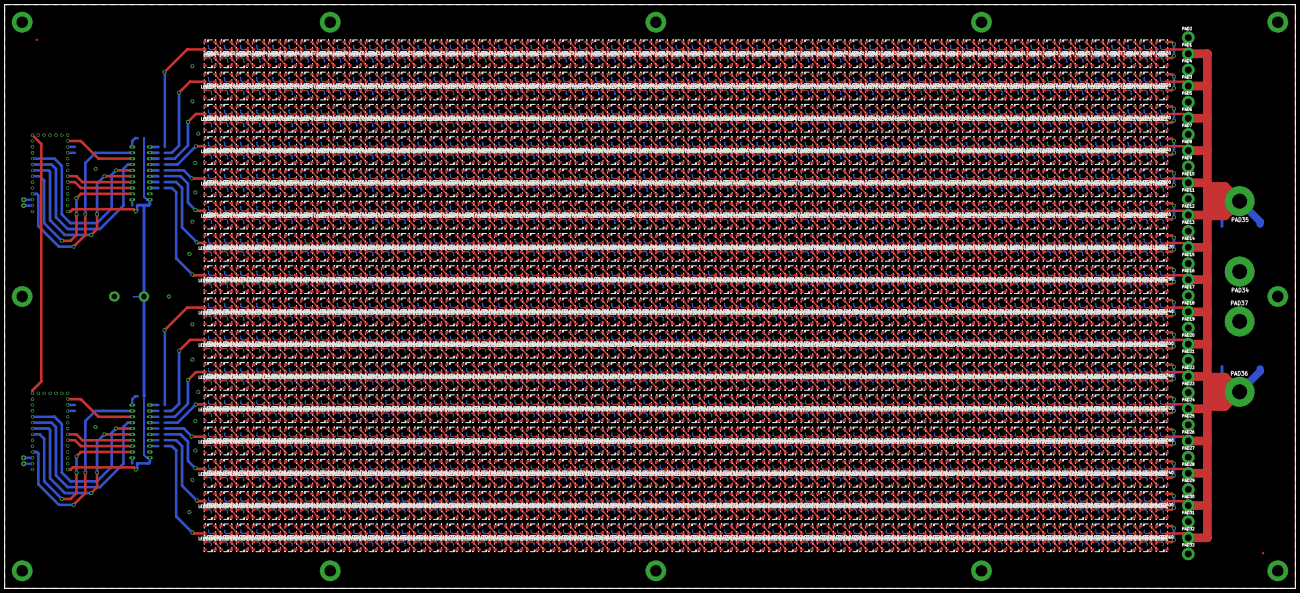
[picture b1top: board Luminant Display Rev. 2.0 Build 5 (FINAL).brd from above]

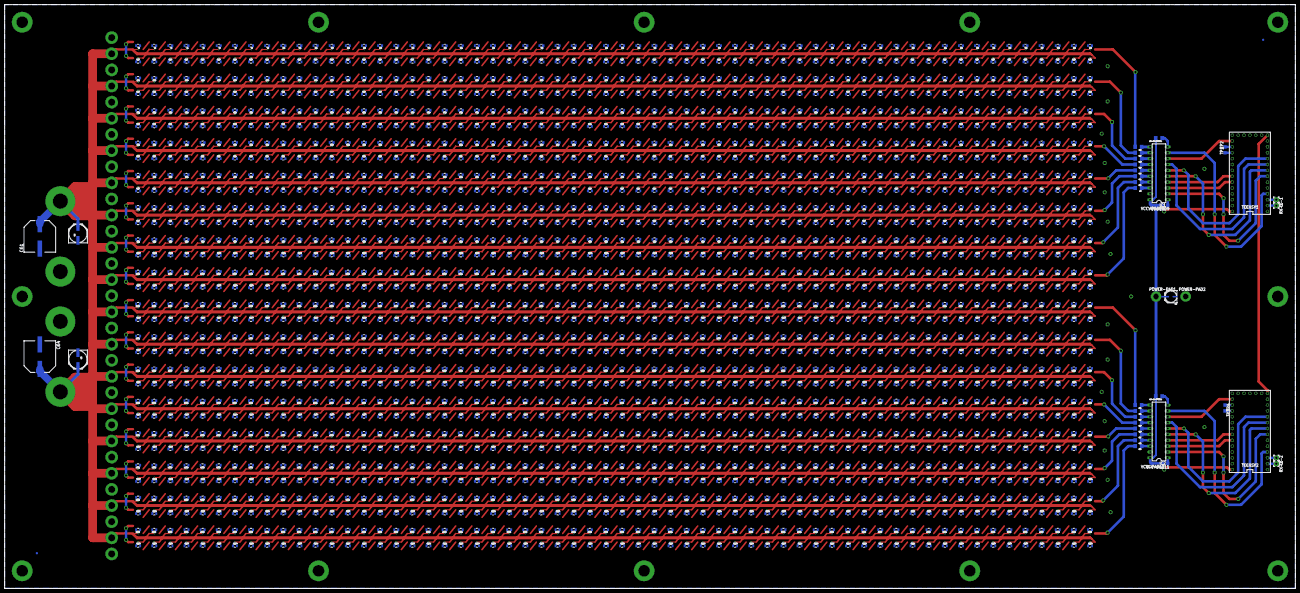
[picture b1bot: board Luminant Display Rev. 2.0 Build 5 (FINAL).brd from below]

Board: 2 copper layers, 558.8 x 252.7 mm, 3922 parts (1963 on the bottom side), 1969 nets.

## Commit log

2014-04-26 Update LICENSE
2014-04-26 HARDWARE Licensing
    Licensing and usage of hardware related designs and components.
2014-04-26 Create BasicRGBTest.ino
    Modified code that incorporates adjustable brightness.
    This test is useful for checking if your LED strips work, and which color config (WS2811_RGB, WS2811_GRB, etc) they require.
2014-04-26 Create AudioVisualizerV2.pde
    This program uses a microphone to provide stunning audio visualizations for the Luminant Display
2014-04-26 Create EnhancedMovie2SerialV2.pde
    Allows the transmitting video data to 1 or more Teensy 3.0+ boards running OctoWS2811 VideoDisplay.ino (provided with the OctoWS2811 library).
2014-04-26 Create MouseDotProgramV2.pde
    This is a recursive painting of a PGraphics object.
2014-04-26 Create GUIDE.md
    A basic guide on how to run Processing programs on Luminant Display
2014-04-26 Rename GUIDE.md to GUIDE
    A basic guide on how to run Processing on Luminant Display Rev. 2.0
2014-04-26 Important information regarding PCB files
    Must have EAGLE Professional to view PCB files.
2014-04-26 Information about Rev. 2.0 PCB files
    Details about the Rev. 2.0 of Luminant Display PCB files
2014-04-26 Luminant Display Rev. 2.0 Board Layout
    This is the version that was sent out for fabrication.
2014-04-26 Luminant Display Rev. 2.0 Schematics
    This is the version that was sent out for fabrication.
2017-09-02 Create AudioVisualizerV2.pde
    Accidental deletion...
    Updated code and commenting for Processing 3.x.x
2017-09-02 Rename AudioVisualizerV2.pde to AudioVisualizerV2.1.pde

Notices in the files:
parts and their libraries:
SparkFun-Passives: Licensing: CC v3.0 Share-Alike You are welcome to use this library for commercial purposes.
